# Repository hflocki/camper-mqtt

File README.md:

<p align="center">
  <picture>
    <source media="(prefers-color-scheme: dark)" srcset="docs/logo/vannode-logo-dark.svg">
    
  </picture>
</p>

# VanNode

🇬🇧 English · 🇩🇪 [Deutsch](README.de.md)

Electronics for a camper van that work together over **MQTT**: tanks, temperatures, batteries, heater, roof fan, roof hatch, levelling and two displays. Every device is an ESP8266/ESP32 with its own **Arduino** firmware, its own web interface and Home Assistant discovery. Devices and displays talk to each other directly through the broker, e.g. the MQTT broker of the LTE router. Home Assistant can listen in, but it does not have to run.

## Why?

It all started with Home Assistant and ESPHome. For the camper, that became too much over time: a server that has to run before anything shows up, a YAML configuration per device, updates that change things on the side, and many parts that all have to fit together. A vehicle is often off-grid for days and runs on battery, so I wanted something simpler and more robust.

So the rules here are:

- **Every device works on its own** – with its own web interface for settings and values, even without a display and without a server.
- **MQTT is the only link.** The broker runs on the router anyway. The displays read straight from the broker.
- **Home Assistant is an option, not a requirement.** Discovery is built in; if you use HA, all devices show up automatically.
- **Updates in the browser**, with a check of the file and a fallback to the previous firmware if something goes wrong.

This is not criticism of ESPHome or Home Assistant – both are great. For this one vehicle a leaner setup simply fit better.

```mermaid
flowchart LR
  broker(("MQTT broker<br/>e.g. RUT956"))
  tank["tanklevel<br/>fresh, grey, gas"] --> broker
  temp["temp<br/>DS18B20 + alarms"] --> broker
  bat["battery<br/>BMS over Bluetooth"] --> broker
  tool["toolbox<br/>Bluetooth plugins: roof hatch …"] <--> broker
  heater["heater<br/>Truma Combi (LIN)"] <--> broker
  fan["maxxfan<br/>VanTurtle"] <--> broker
  level["level<br/>BNO085 + wedges"] <--> broker
  omg["omg<br/>BLE thermometers"] -.-> broker
  broker <--> display["display<br/>4-inch wall panel + web page"]
  broker --> rb["roadbuddy<br/>M5Stack Core2"]
  broker -.- ha["Home Assistant<br/>(optional)"]
```

## Devices

| Folder | Hardware | Purpose | Base topic |
| --- | --- | --- | --- |
| [`firmware/tanklevel`](firmware/tanklevel) | ESP32-C3 | Fresh and grey water (Votronic), gas bottle (BLE) | `camper/tanklevel` |
| [`firmware/temp`](firmware/temp) | ESP8266 / ESP32-C3 | up to 8 DS18B20 (fridge, freezer …) with alarm limits | `camper/temp` |
| [`firmware/battery`](firmware/battery) | ESP32-C3 | Battery BMS over Bluetooth (Daly, Ective BM X): state of charge, current, cells | `camper/battery` |
| [`firmware/toolbox`](firmware/toolbox) | ESP32-C3 | Bluetooth devices as plugins: RV Tech roof hatch (Heki), CaraWater pump, WCS fridge | `camper/toolbox` |
| [`firmware/heater`](firmware/heater) | ESP32 + LIN transceiver | Truma Combi / Vario Heat as an iNet Box on the CP Plus | `camper/heater` |
| [`firmware/maxxfan`](firmware/maxxfan) | ESP32-C3 + VanTurtle | MaxxFan roof fan | `camper/maxxfan` |
| [`firmware/level`](firmware/level) | ESP32 + BNO085 | Pitch, roll and wedge height for every wheel (fork of the level sensor by klehnst) | `camper/level` |
| [`firmware/omg`](firmware/omg) | ESP32 / ESP32-C3 | Bluetooth thermometers (Govee, Ruuvi, Xiaomi …) through OpenMQTTGateway | `camper/OMG` |
| [`firmware/display`](firmware/display) | Guition ESP32-4848S040 | 4" wall panel + the same page for the phone: shows and controls everything, weather, warnings, Pushover | `camper/display` |
| [`firmware/roadbuddy`](firmware/roadbuddy) | M5Stack Core2 | small battery display: levelling, water, gas | – (receive only) |

Not in this repo: **router data (GPS, mobile signal)** is sent by the RUT956 itself over MQTT, see [router data in the display README](firmware/display/README.md#router-daten-rut956).

- **Testing at home:** [`tools/emulator`](tools/emulator) is a Python tool with a local web page. It sends the topics of all devices, the router and Zigbee with values you can change, plus scenarios (tanks running empty, departure, a device dropping out …), so the displays can be tested without the vehicle
- All topics at a glance: [`docs/TOPICS.md`](docs/TOPICS.md)
- Clickable mockups of every web interface: [`docs/mockups/`](docs/mockups/index.html)
- Notes for AI assistants and contributors: [`AGENTS.md`](AGENTS.md)

The documentation of the individual devices and the web interfaces are in German.

## Quick start

1. **Get the firmware:** download the device's `.bin` from [Releases](https://github.com/hflocki/vannode/releases) – or build it yourself (Arduino IDE or `arduino-cli`; board and libraries are listed in the device README).
2. **Flash once over USB.** After that, updates go through the web interface.
3. **Set up:** without WiFi credentials the device opens an access point `<device>-Node-XXXXXX`. Connect, open `http://192.168.4.1`, enter WiFi and MQTT broker.
4. The device appears under `camper/<device>/…` on the broker; the display finds it by itself.

## Common rules

All devices follow the same scheme, so the displays and Home Assistant understand them without special cases:

| What | How |
| --- | --- |
| Topics | `camper/<device>/…`, values **retained** |
| Availability | `camper/<device>/status` = `online` / `offline` as last will (retained, QoS 1) |
| Diagnostics | `camper/<device>/info`: JSON with version, IP, signal, uptime |
| Commands | `…/cmd/…` or `…/set/…`, not retained |
| Home Assistant | auto discovery under `homeassistant/…`, one device per firmware |
| Setup | access point `<device>-Node-XXXXXX`, settings in the browser at `http://192.168.4.1` |
| Web interface | same look on every device, optional login (HTTP basic auth); forgot the login → `noauth` in the serial monitor or factory reset |
| Updates | in the browser, with checks (wrong device, `.merged.bin`, too large), event log and fallback to the previous firmware |
| Firmware version | `FW_VERSION` in the device's `config.h`, shown in the web UI and in HA |

## Your own settings (`config_local.h`)

Passwords, WiFi and broker do not belong in the repo. Next to its `config.h`, every device has a template `config_local.h.example`:

```bash
cd firmware/temp/camper_temp
cp config_local.h.example config_local.h   # then edit
```

Everything in `config_local.h` replaces the default from `config.h`. The file is excluded by `.gitignore`, so it never ends up on GitHub, and updates or patches do not overwrite it. Typical values:

| Value | Effect |
| --- | --- |
| `DEFAULT_AP_PASSWORD` | password of the setup access point |
| `DEFAULT_OTA_PASSWORD` | password for updates through the network port of the Arduino IDE |
| `DEFAULT_WIFI_SSID` / `DEFAULT_WIFI_PASSWORD` | WiFi a freshly flashed device joins right away |
| `DEFAULT_MQTT_SERVER`, `_USER`, `_PASSWORD` | factory broker |
| `DEFAULT_WEB_USER` / `DEFAULT_WEB_PASSWORD` | factory login for the web interface |

Any other value from `config.h` can be overridden as well (pins, prefix, tank size …).

Note: factory WiFi, MQTT and login only apply while nothing is stored on the device yet. A normal update over existing settings does not change them. They are taken over again after a **factory reset** in the web UI, after flashing with **Erase All Flash Before Sketch Upload: Enabled** (Arduino IDE, Tools menu), or for temp, tanklevel, level and battery after uploading the LittleFS image. The access point and OTA passwords always apply immediately.

The Road Buddy has no settings page, only an update page; there the whole `config.h` is the personal file (template `config.example.h`). A firmware built with your own `config.h` stores the credentials in flash, so the Actions firmware can be installed through the update page afterwards.

## Warnings

`firmware/temp` reports exceeded limits (e.g. "fridge above 8 °C for 15 min") under `camper/temp/alarm_text`. The wall panel shows these, heater errors and battery, tank, frost and weather warnings in the status tile and as a yellow banner in the header – optionally also as a **Pushover** message on the phone, with its own priority per kind of warning, up to an emergency that keeps ringing until it is confirmed. Home Assistant gets the same alarms as binary sensors.

## Ready-made firmware

Every push builds all devices with GitHub Actions ([`.github/workflows/build.yml`](.github/workflows/build.yml)), using exactly the board package and library versions from the device READMEs. The `.bin` files are available in the **Actions** tab of each run.

A release for **one** device is made with a tag `<device>-v<version>`:

```bash
git tag temp-v1.1.0
git push origin temp-v1.1.0
```

Then only this device is built and the `.bin` is attached to the release. All devices install it through their web interface (Road Buddy through its update page). For temp, tanklevel, level, battery, maxxfan and toolbox the web interface also lives as `data/index.html.gz` in the sketch folder and is uploaded separately after an update.

**Names:** every device is called `<device>-node` – hostname (`temp-node.local`), setup access point (`Temp-Node-XXXXXX`) and release file (`temp-node-esp32c3.bin`). MQTT topics stay `camper/<device>/…`, Home Assistant IDs stay unchanged.

**All devices in one release:** a tag `bundle-v<version>` builds every device and creates one release with the files listed in [`.github/bundle.txt`](.github/bundle.txt) (one device and target per line, e.g. `heater esp32`), plus the web pages as `<device>-node-web.html.gz` and a table of all versions.

```bash
git tag bundle-v2026.11.07
git push origin bundle-v2026.11.07
```

## Build just one device

Take the device folder and follow its README. If you do not want the whole repo:

```bash
git clone --filter=blob:none --sparse https://github.com/hflocki/vannode.git
cd vannode
git sparse-checkout set firmware/temp
```

## New device

[`firmware/_template`](firmware/_template) is a working sample device with everything shared (WiFi with setup access point, web interface, settings, MQTT with Home Assistant discovery, updates without USB). One command copies it as a new device; then you only fill in the sensor part (`sensor.cpp`). Guide (German): [`firmware/_template/ANLEITUNG.md`](firmware/_template/ANLEITUNG.md).

```bash
python firmware/_template/tools/new_device.py waste "Abwasser"
```

Every folder is complete on its own: its own README with hardware, board settings, libraries and topics, the Arduino sketch in a subfolder named like the `.ino` (e.g. `camper_temp/`, heater `truma_heater/`). Everything is built with Arduino (IDE or `arduino-cli`); PlatformIO is only used for the Bluetooth gateway `firmware/omg`, because OpenMQTTGateway is a third-party PlatformIO project.

## Mockups

[`docs/mockups/`](docs/mockups/index.html) has a clickable mockup of every web interface: the real page from the firmware with simulated data. Buttons, settings, saving and uploads react like on the device, but nothing is sent. `index.html` shows all devices side by side in phone size. The design draft that all pages follow (colours, type, icons, building blocks, plus drafts of the display page) is in [`docs/mockups/design/`](docs/mockups/design/system.html) and linked from the same index.

To view them, download the folder and open `index.html` in a browser. Regenerate after changing a web interface (Python standard library only, no venv needed):

```bash
python3 tools/mockups/make_mockups.py
```

Sample data and simulated behaviour per device are in `tools/mockups/mock/<device>.js`, the shared part (fetch, WebSocket, upload) in `core.js`. For a new device, add a file there and register it in `make_mockups.py`. The Road Buddy only has a small update page and is therefore missing.

## Origin

The devices used to be separate repos (`camper-tanklevel`, `camper-temp`, `camper-heater`, `camper-maxxfan`, `camper-display`, `m5core2-roadbuddy`, `camper_toolbox`). They were moved here; the old repos are or will be archived.

## Licenses

Every folder keeps its license:

| Folder | License |
| --- | --- |
| `firmware/battery` | Apache-2.0 (protocols ported from [aiobmsble](https://github.com/patman15/aiobmsble)) |
| `firmware/heater` | GPL-3.0 (protocol logic ported from GPL projects, see its README) |
| `firmware/level` | MIT ([klehnst](https://github.com/klehnst/ESP32-Adrafruit-BNO085-HomeAssistant-Caravan-Levelsensor-MQTT)) |
| `firmware/tanklevel`, `temp`, `maxxfan`, `display` | MIT |
| `firmware/toolbox` | MIT (roof hatch protocol ported from the HA integration rvtech-hacs) |
| `firmware/roadbuddy` | MIT |

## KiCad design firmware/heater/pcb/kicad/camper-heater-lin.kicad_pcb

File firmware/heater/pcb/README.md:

# camper-heater LIN – eigene Platine

Fertig bestückbare Platine für die camper-heater-Firmware: ESP32-C3-Modul, LIN-Transceiver, geschützte 12-V-Versorgung, USB-C zum Flashen und zwei RJ12-Buchsen. Der ESP meldet sich wie eine iNet Box als **Slave** an, das **CP Plus bleibt Master** und voll bedienbar.

> **Stand: Version 1.0, noch nicht gefertigt und nicht getestet.** Die Daten bestehen den Design-Check von KiCad (keine Fehler, alle Verbindungen geroutet). Für die erste Bestellung die kleinste Stückzahl wählen (5 Platinen, 2 davon bestückt) und vor dem Einbau die Prüfschritte unten machen.

| Oberseite | Unterseite |
| --- | --- |
|  |  |

Schaltplan: [`docs/schaltplan.pdf`](docs/schaltplan.pdf) · Gerber-Vorschau: [`docs/ansicht-gerber.png`](docs/ansicht-gerber.png)

## Was drauf ist

| Block | Bauteile | Zweck |
| --- | --- | --- |
| 12-V-Eingang | J1 Schraubklemme, **F1 Mini-Flachsicherung 1 A**, D1 Verpolschutz (Schottky 100 V), D2 TVS SMBJ22A | Kurzschluss, Verpolung und Spannungsspitzen beim Motorstart oder Laden |
| Versorgung | PS1 RECOM R-78HB5.0-0.5 (9–72 V → 5 V), D3/D4 + U3 AP2112K-3.3 | fertiges Wandler-Modul für Fahrzeugbordnetze, 3,3 V für den ESP. Strom wahlweise aus 12 V **oder** USB |
| ESP32 | U1 ESP32-C3-WROOM-02-N4, Taster RESET und BOOT, 3 LEDs | Antenne am Platinenrand, darunter kein Kupfer |
| LIN | U2 TJA1021T/20, C11 220 pF, Pull-ups | Slave-Beschaltung ohne Master-Widerstand, wie eine iNet Box |
| Bus | J2 + J3 RJ12 6P6C, alle 6 Kontakte 1:1 verbunden | Pin 3 = LIN, Pin 5 = Masse (wie bei havanti/esphome-truma) |
| USB-C | J4, U4 USBLC6-2SC6 | Flashen, serielles Log, Strom am Schreibtisch |

Maße: **75 × 66 mm**, 2 Lagen, 4 Befestigungslöcher M3. GPIO-Belegung: GPIO4 = LIN TX, GPIO3 = LIN RX, GPIO5 = SLP, GPIO6 = LED LIN (blau), GPIO7 = LED MQTT (gelb), grüne LED = 3,3 V vorhanden.

## Bestellen bei PCBWay

Dateien in [`fertigung/`](fertigung):

| Datei | Wohin bei PCBWay |
| --- | --- |
| `camper-heater-lin-gerber.zip` | „Quick-order PCB“ → **Add Gerber File** |
| `camper-heater-lin-bom.xlsx` | Assembly → **BOM** |
| `camper-heater-lin-cpl.csv` | Assembly → **Centroid / Pick & Place** |

**Platine** (Werte, die PCBWay beim Gerber meist selbst erkennt):
- Layers: **2**, Size: **75 × 66 mm**, Material: FR-4 TG130–150, Thickness: **1,6 mm**
- Min track/spacing: **6/6 mil** (Design nutzt 0,2 mm), Min hole size: **0,3 mm**
- Solder mask: beliebig (z. B. grün), Silkscreen: weiß, Surface finish: **HASL lead free**
- Copper weight: 1 oz, Via: tented, keine Sonderoptionen

**Bestückung** (Assembly Service anhaken):
- **Turnkey** (PCBWay besorgt alle Teile), Assembly side: **Top side**
- Number of unique parts: **28**, SMD-Teile **und** Through-Hole-Teile (J1, J2, J3, F1, PS1) → „Both“
- Quantity: z. B. **2**
- Bemerkung, die man ins Feld „Notes“ kopieren kann:
  > Please do not place JP1 (open solder jumper) and test points TP1–TP5, they are pads only. Fuse holder F1: only the holder (Keystone 3568), no fuse. Fiducials FID1/FID2 on top side. Please check the rotation of U1, U2, U3, U4 and the diodes against the silkscreen marks.

PCBWay prüft BOM und Bestückungsdatei vor der Fertigung und meldet sich bei Rückfragen, z. B. wenn ein Teil nicht lieferbar ist und ein Ersatz vorgeschlagen wird. Gleichwertige Ersatzteile sind in Ordnung, solange **Spannungsfestigkeit und Gehäuse** gleich bleiben (D2 SMBJ22A, C1 50 V, PS1 R-78HB5.0-0.5).

**Dazu kaufen:** eine Mini-Flachsicherung (ATM) **1 A**, ein kurzes RJ12-Kabel 6P6C (6 Adern, nicht nur 4), Kabel für 12 V und Masse.

## Vor dem ersten Einbau prüfen

1. **Sichtprüfung:** D1, D2 (Strich = Kathode) und U1–U4 wie auf dem Bestückungsdruck.
2. **Ohne Sicherung** mit dem Multimeter messen: J1 Pin 1 gegen Pin 2 darf **kein Kurzschluss** sein, ebenso TP1 (VBAT), TP2 (5 V) und TP3 (3,3 V) gegen TP4 (GND).
3. **Nur USB** anstecken (ohne 12 V): grüne LED an, TP3 ≈ 3,3 V. Firmware flashen (siehe unten).
4. **12 V über ein Labornetzteil mit Strombegrenzung** (z. B. 100 mA) oder direkt mit eingesetzter 1-A-Sicherung: TP1 ≈ 11,7 V, TP2 ≈ 4,7 V, TP3 = 3,3 V. Strom im Leerlauf rund 30–80 mA bei 12 V.
5. **RJ12-Kabel messen, bevor JP1 geschlossen wird:** Im Fahrzeug bei eingeschaltetem CP Plus am freien RJ12-Anschluss messen. Pin 5 muss 0 V gegen Fahrzeugmasse haben, Pin 3 (LIN) liegt in Ruhe bei etwa Bordspannung. **JP1 bleibt offen**, die Masse kommt über J1. Nur wenn die Verbindung ohne JP1 nicht klappt und Pin 5 nachgemessen Masse ist, JP1 mit einem Lötklecks schließen.

## Anschluss im Camper

- **Einfachster Weg:** Nur **J2** benutzen und mit einem RJ12-Kabel an die **freie Zubehörbuchse der Combi** stecken (dort steckt sonst die iNet Box). J3 bleibt frei.
- **Durchschleifen:** CP Plus → J2 und J3 → Heizung. Die Platine verhält sich dann wie ein 6-poliger Y-Verteiler. Dafür beide Kabel gleicher Art nehmen (beide 1:1 oder beide gekreuzt).
- **12 V:** J1 Pin 1 (+12 V) mit Plus aus dem Sicherungsverteiler, Pin 2 mit Masse. Die 1-A-Sicherung sitzt auf der Platine; eine zweite Sicherung am Verteiler schadet nicht.

## Firmware

Im Sketch [`../truma_heater/config.h`](../truma_heater/config.h) das Board-Profil wählen, am besten in `config_local.h`:

```cpp
#define BOARD_CAMPER_LIN_C3
```

Arduino IDE: Board **ESP32C3 Dev Module**, USB CDC On Boot **Enabled**, Partition Scheme **Minimal SPIFFS**. Zum ersten Flashen BOOT gedrückt halten, RESET kurz drücken, BOOT loslassen. Danach geht jedes Update per Web-UI oder OTA.

Am CP Plus einmal anmelden: Einstellungen → **RESET → PR SET**. Siehe [Inbetriebnahme](../README.md#inbetriebnahme).

## Selbst ändern

Die Platine wird komplett aus Skripten erzeugt, damit Änderungen nachvollziehbar bleiben:

| Datei | Inhalt |
| --- | --- |
| `tools/parts.py` | Bauteile, Teilenummern und alle Verbindungen (eine Quelle für Platine, BOM und Schaltplan) |
| `tools/place.py` | Positionen, Platinenumriss, Netzklassen, Beschriftung |
| `tools/route.py` | Autorouter (Freerouting) und Import |
| `tools/finish.py` | Masseflächen oben und unten, Durchkontaktierungen |
| `tools/make_outputs.py` | Gerber, Bohrdaten, BOM, Bestückungsdatei |
| `tools/schematic.py` | Schaltplan als PDF/SVG |
| `kicad/camper-heater-lin.kicad_pcb` | fertige Platine zum Öffnen in KiCad 7 oder neuer |

Neu bauen (Linux mit KiCad 7, Java 17+ und `xvfb-run`):

```bash
cd firmware/heater/pcb/tools
curl -LO https://github.com/freerouting/freerouting/releases/download/v1.9.0/freerouting-1.9.0.jar && mv freerouting-1.9.0.jar freerouting.jar
python3 -m venv --system-site-packages .venv && source .venv/bin/activate && pip install -r requirements.txt
./build_all.sh
```

Kleine Änderungen (Beschriftung, eine Leiterbahn) gehen auch direkt in KiCad an `kicad/camper-heater-lin.kicad_pcb`; danach in KiCad den Design-Check laufen lassen und die Fertigungsdateien neu exportieren.

## Lizenz

Wie der Rest von `firmware/heater`: GPL-3.0.

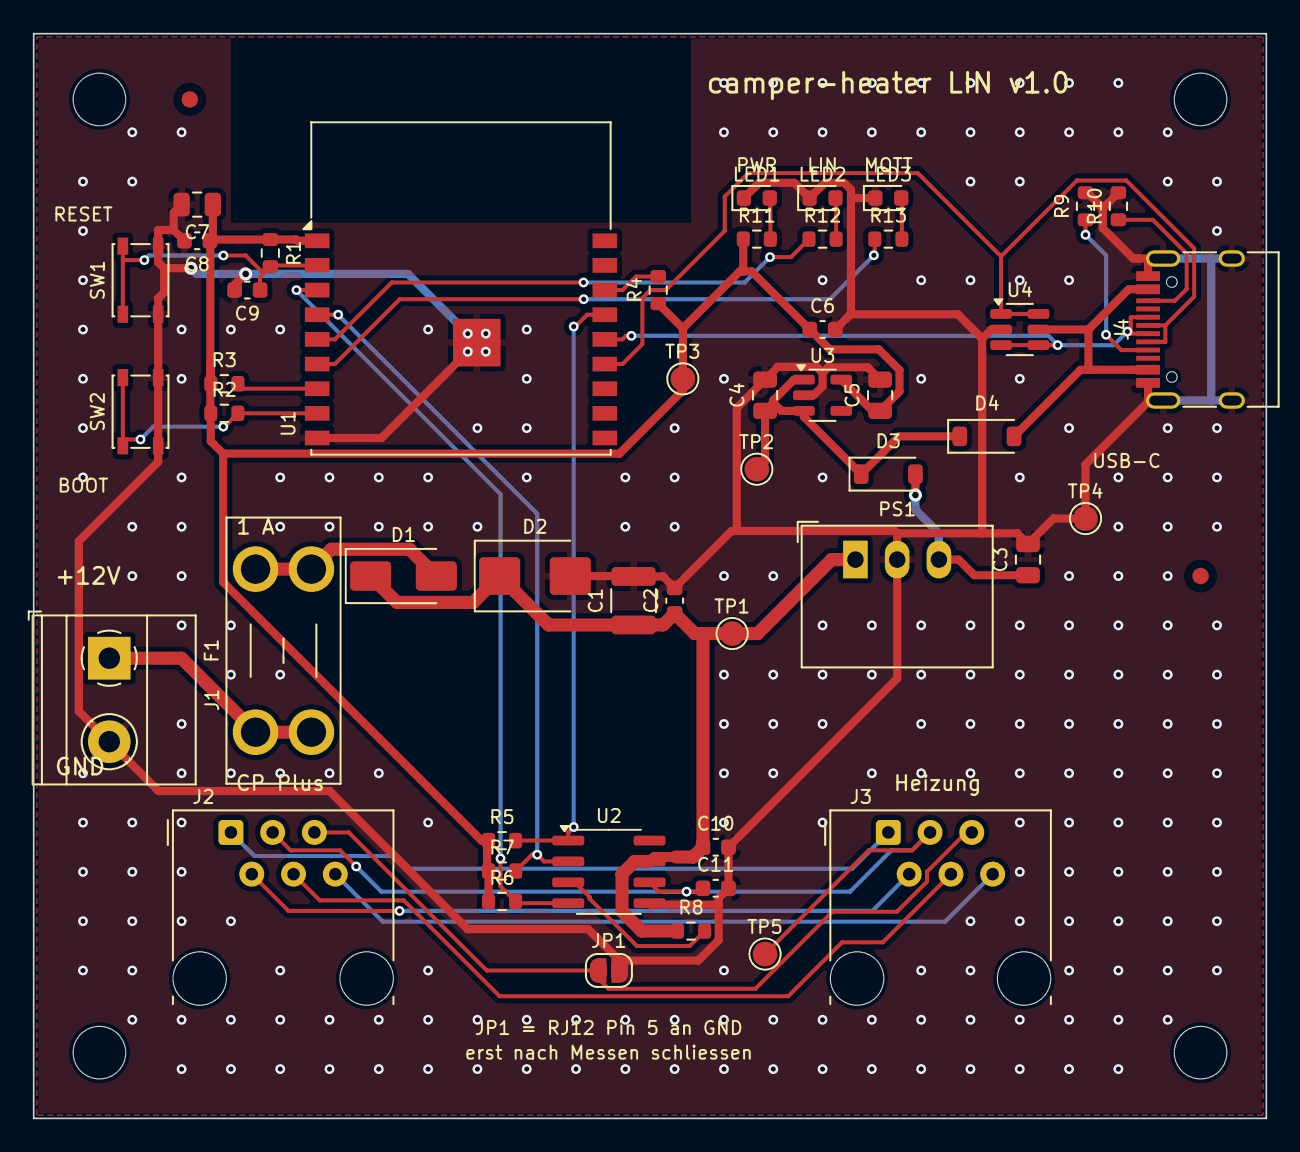
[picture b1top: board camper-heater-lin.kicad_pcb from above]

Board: 2 copper layers, 75.0 x 66.0 mm, 55 parts (0 on the bottom side), 31 nets.

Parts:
C1: 10uF 50V; C_1210_3225Metric
C2, C6, C8, C10: 100nF 50V; C_0603_1608Metric
C3, C5, C7: 22uF 10V; C_0805_2012Metric
C4: 10uF 10V; C_0805_2012Metric
C9: 1uF; C_0603_1608Metric
C11: 220pF 50V; C_0603_1608Metric
D1: B1100; D_SMA
D2: SMBJ22A; D_SMB
D3, D4: B5819W; D_SOD-123
F1: Mini-Flachsicherung 1 A; Fuseholder_Blade_Mini_Keystone_3568
FID1, FID2: Fiducial; Fiducial_1mm_Mask2mm
H1, H2, H3, H4: M3; MountingHole_3.2mm_M3
J1: 12V IN; TerminalBlock_Phoenix_MKDS-1,5-2-5.08_1x02_P5.08mm_Horizont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
J2: RJ12 (CP Plus); RJ12_Amphenol_54601-x06_Horizontal
J3: RJ12 (Heizung); RJ12_Amphenol_54601-x06_Horizontal
J4: USB-C; USB_C_Receptacle_HRO_TYPE-C-31-M-12
JP1: RJ12 Pin 5 an GND; SolderJumper-2_P1.3mm_Open_RoundedPad1.0x1.5mm
LED1: grün (Power); LED_0603_1608Metric
LED2: blau (LIN); LED_0603_1608Metric
LED3: gelb (MQTT); LED_0603_1608Metric
PS1: R-78HB5.0-0.5; Converter_DCDC_RECOM_R-78HB-0.5_THT
R1, R2, R3, R4, R6, R7, R8: 10k; R_0603_1608Metric
R5: 4.7k; R_0603_1608Metric
R9, R10: 5.1k; R_0603_1608Metric
R11, R12, R13: 1k; R_0603_1608Metric
SW1: RESET; SW_SPST_PTS810
SW2: BOOT; SW_SPST_PTS810
TP1: VBAT; TestPoint_Pad_D1.5mm
TP2: 5V; TestPoint_Pad_D1.5mm
TP3: 3V3; TestPoint_Pad_D1.5mm
TP4: GND; TestPoint_Pad_D1.5mm
TP5: LIN; TestPoint_Pad_D1.5mm
U1: ESP32-C3-WROOM-02-N4; ESP32-C3-WROOM-02
U2: TJA1021T/20; SOIC-8_3.9x4.9mm_P1.27mm
U3: AP2112K-3.3; SOT-23-5
U4: USBLC6-2SC6; SOT-23-6

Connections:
+3V3: C5.1, C6.1, C7.1, C8.1, R1.1, R2.1, R3.1, R4.1, R5.1, R6.1, R7.1, R11.1, TP3.1, U1.1, U3.5
+5V: C4.1, D3.1, D4.1, TP2.1, U3.1, U3.3
+5V_DC: C3.1, D3.2, PS1.3
CC1: J4.A5, R9.1
CC2: J4.B5, R10.1
EN: C9.1, R1.2, SW1.1, U1.2
GND: C1.2, C2.2, C3.2, C4.2, C5.2, C6.2, C7.2, C8.2, C9.2, C10.2, C11.2, D2.2, J1.2, J4.A1, J4.A12, J4.B1, J4.B12, J4.S1, JP1.2, LED1.1, LED2.1, LED3.1, PS1.2, R9.2, R10.2, SW1.2, SW2.2, TP4.1, U1.9, U1.19, U2.5, U3.2, U4.2
IO2: R4.2, U1.16
IO8: R3.2, U1.7
IO9: R2.2, SW2.1, U1.8
LED1_A: LED1.2, R11.2
LED2_A: LED2.2, R12.2
LED3_A: LED3.2, R13.2
LED_LIN: R12.1, U1.5
LED_MQTT: R13.1, U1.6
LIN: C11.1, J2.3, J3.3, TP5.1, U2.6
LIN_RX: R5.2, U1.15, U2.1
LIN_SLP: R7.2, U1.4, U2.2
LIN_TX: R6.2, U1.3, U2.4
LIN_WAKE: R8.2, U2.3
RJ1: J2.1, J3.1
RJ2: J2.2, J3.2
RJ4: J2.4, J3.4
RJ5: J2.5, J3.5, JP1.1
RJ6: J2.6, J3.6
USB_DN: J4.A7, J4.B7, U1.13, U4.1, U4.6
USB_DP: J4.A6, J4.B6, U1.14, U4.3, U4.4
VBAT: C1.1, C2.1, C10.1, D1.1, D2.1, PS1.1, R8.1, TP1.1, U2.7
VBUS: D4.2, J4.A4, J4.A9, J4.B4, J4.B9, U4.5
VIN_F: D1.2, F1.2
VIN_RAW: F1.1, J1.1

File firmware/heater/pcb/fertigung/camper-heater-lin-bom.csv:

Item #,Designator,Qty,Manufacturer,Mfg Part #,Description / Value,Package / Footprint,Type,Hinweis
1,C1,1,Murata,GRM32ER71H106KA12L,10uF 50V – Keramikkondensator,C_1210_3225Metric,SMD,
2,"C2,C6,C8,C10",4,Murata,GRM188R71H104KA93D,100nF 50V – Keramikkondensator,C_0603_1608Metric,SMD,
3,"C3,C5,C7",3,Murata,GRM21BR61A226ME44L,22uF 10V – Keramikkondensator,C_0805_2012Metric,SMD,
4,C4,1,Murata,GRM21BR61A106KE19L,10uF 10V – Keramikkondensator,C_0805_2012Metric,SMD,
5,C9,1,Murata,GRM188R71C105KA12D,1uF – Keramikkondensator,C_0603_1608Metric,SMD,
6,C11,1,Murata,GRM1885C1H221JA01D,220pF 50V – Keramikkondensator,C_0603_1608Metric,SMD,
7,D1,1,Diodes Inc.,B1100-13-F,"B1100 – Schottky 100 V 1 A, Verpolschutz",D_SMA,SMD,
8,D2,1,Littelfuse,SMBJ22A,"SMBJ22A – TVS 22 V, Schutz gegen Spannungsspitzen",D_SMB,SMD,
9,"D3,D4",2,Diodes Inc.,B5819W,B5819W – Schottky 40 V 1 A (Wandler -> 5 V),D_SOD-123,SMD,
10,F1,1,Keystone,3568,"Mini-Flachsicherung 1 A – Sicherungshalter Mini-Flachsicherung (ATM), Sicherung 1 A lose dazu",Fuseholder_Blade_Mini_Keystone_3568,THT,"Nur der Halter wird bestückt. Sicherung 1 A (Mini-Flachsicherung ATM, z. B. Littelfuse 0297001.WXNV) lose beilegen oder selbst einstecken."
11,J1,1,Phoenix Contact,1715734,"12V IN – Schraubklemme 2-pol. 5,08 mm (1 = +12 V, 2 = Masse)","TerminalBlock_Phoenix_MKDS-1,5-2-5.08_1x02_P5.08mm_Horizontal",THT,
12,J2,1,Amphenol,54601-906WPLF,RJ12 (CP Plus) – RJ12 6P6C Buchse,RJ12_Amphenol_54601-x06_Horizontal,THT,
13,J3,1,Amphenol,54601-906WPLF,RJ12 (Heizung) – RJ12 6P6C Buchse,RJ12_Amphenol_54601-x06_Horizontal,THT,
14,J4,1,Korean Hroparts,TYPE-C-31-M-12,USB-C – USB-C Buchse 16-pol.,USB_C_Receptacle_HRO_TYPE-C-31-M-12,SMD,
15,LED1,1,Würth,150060VS75000,grün (Power) – LED grün,LED_0603_1608Metric,SMD,
16,LED2,1,Würth,150060BS75000,blau (LIN) – LED blau,LED_0603_1608Metric,SMD,
17,LED3,1,Würth,150060YS75000,gelb (MQTT) – LED gelb,LED_0603_1608Metric,SMD,
18,PS1,1,RECOM,R-78HB5.0-0.5,"R-78HB5.0-0.5 – Schaltregler-Modul 9-72 V -> 5 V 0,5 A",Converter_DCDC_RECOM_R-78HB-0.5_THT,THT,
19,"R1,R2,R3,R4,R6,R7,R8",7,Yageo,RC0603FR-0710KL,"10k – Widerstand 1 %, 0603",R_0603_1608Metric,SMD,
20,R5,1,Yageo,RC0603FR-074K7L,"4.7k – Widerstand 1 %, 0603",R_0603_1608Metric,SMD,
21,"R9,R10",2,Yageo,RC0603FR-075K1L,"5.1k – Widerstand 1 %, 0603",R_0603_1608Metric,SMD,
22,"R11,R12,R13",3,Yageo,RC0603FR-071KL,"1k – Widerstand 1 %, 0603",R_0603_1608Metric,SMD,
23,SW1,1,C&K,PTS810 SJM 250 SMTR LFS,RESET – Taster Neustart,SW_SPST_PTS810,SMD,
24,SW2,1,C&K,PTS810 SJM 250 SMTR LFS,BOOT – Taster Boot (Flash-Modus),SW_SPST_PTS810,SMD,
25,U1,1,Espressif,ESP32-C3-WROOM-02-N4,"ESP32-C3-WROOM-02-N4 – WLAN-Modul ESP32-C3, 4 MB Flash",ESP32-C3-WROOM-02,SMD,"Antenne zeigt zum Platinenrand, unter der Antenne kein Kupfer."
26,U2,1,NXP,"TJA1021T/20/C,118",TJA1021T/20 – LIN-Transceiver,SOIC-8_3.9x4.9mm_P1.27mm,SMD,"Gleichwertig: TJA1021T/20/C,118 oder TJA1021T/10 (LIN 2.x Slave)."
27,U3,1,Diodes Inc.,AP2112K-3.3TRG1,"AP2112K-3.3 – LDO 3,3 V 600 mA",SOT-23-5,SMD,
28,U4,1,STMicroelectronics,USBLC6-2SC6,USBLC6-2SC6 – ESD-Schutz USB,SOT-23-6,SMD,

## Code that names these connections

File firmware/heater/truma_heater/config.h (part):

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    !defined(BOARD_ESP32_DEVKIT)
// #define BOARD_SMARTAVAN       // smartavan heater controller (Arduino board: "ESP32 Dev Module")
// #define BOARD_ESP32_GENERIC   // ESP32 DevKit + TJA1020/1021 module, inetbox2mqtt wiring (Arduino board: "ESP32 Dev Module")
// #define BOARD_ESP32_DEVKIT    // ESP32 DevKit (WROOM-32) + LIN module, TX 16 / RX 17 (Arduino board: "ESP32 Dev Module")
// #define BOARD_ESP32S3_GENERIC // ESP32-S3 DevKit + LIN module (Arduino board: "ESP32S3 Dev Module")
// #define BOARD_ESP32C3_GENERIC // ESP32-C3 + LIN module (Arduino board: "ESP32C3 Dev Module")
// #define BOARD_ESP32C3_SUPERMINI  // ESP32-C3 Super Mini + LIN module (Arduino board: "ESP32C3 Dev Module")
// #define BOARD_CAMPER_LIN_C3   // own LIN board with ESP32-C3-WROOM-02 + TJA1021 (Arduino board: "ESP32C3 Dev Module")
// Nothing selected: the default board of the chip the sketch is built for (also what CI builds)
#if CONFIG_IDF_TARGET_ESP32
#define BOARD_ESP32_DEVKIT
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#ifndef LIN_UART_NUM
#define LIN_UART_NUM UART_NUM_2
#endif
#ifndef LIN_TX_PIN
#define LIN_TX_PIN 16
#endif
#ifndef LIN_RX_PIN
#define LIN_RX_PIN 17
#endif

#elif defined(BOARD_ESP32_GENERIC)
// Plain ESP32 DevKit + TJA1020/TJA1021 module, wiring as in mc0110/inetbox2mqtt ("ESP32" profile)
#define BOARD_NAME "ESP32 + LIN module"
#ifndef LIN_UART_NUM
#define LIN_UART_NUM UART_NUM_2
#endif
#ifndef LIN_TX_PIN
#define LIN_TX_PIN 17
#endif
#ifndef LIN_RX_PIN
#define LIN_RX_PIN 16
#endif
#ifndef MQTT_LED_PIN
#define MQTT_LED_PIN 4
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#elif defined(BOARD_ESP32_DEVKIT)
// ESP32 DevKit V4 (ESP32-WROOM-32) + TJA1020 module (e.g. FST T151), supplied with 5 V from a buck converter.
// ESP TX GPIO16 -> module TX (TXD), module RX (RXD) -> ESP RX GPIO17. Module SLP to 3V3.
#define BOARD_NAME "Heater Node (ESP32 DevKit + LIN module)"
#ifndef LIN_UART_NUM
#define LIN_UART_NUM UART_NUM_2
#endif
#ifndef LIN_TX_PIN
#define LIN_TX_PIN 16
#endif
#ifndef LIN_RX_PIN
#define LIN_RX_PIN 17
#endif

#elif defined(BOARD_ESP32S3_GENERIC)
// ESP32-S3 DevKit + LIN module (any free GPIOs, adjust with build flags)
#define BOARD_NAME "ESP32-S3 + LIN module"
#ifndef LIN_UART_NUM
#define LIN_UART_NUM UART_NUM_1
#endif
#ifndef LIN_TX_PIN
#define LIN_TX_PIN 17
#endif
#ifndef LIN_RX_PIN
#define LIN_RX_PIN 18
#endif

#elif defined(BOARD_ESP32C3_GENERIC)
// ESP32-C3 (single core, UART0/1 only) + LIN module
#define BOARD_NAME "ESP32-C3 + LIN module"
#ifndef LIN_UART_NUM
#define LIN_UART_NUM UART_NUM_1
#endif
#ifndef LIN_TX_PIN
#define LIN_TX_PIN 21
#endif
#ifndef LIN_RX_PIN
#define LIN_RX_PIN 20
#endif

#elif defined(BOARD_ESP32C3_SUPERMINI)
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#ifndef LIN_UART_NUM
#define LIN_UART_NUM UART_NUM_1
#endif
#ifndef LIN_TX_PIN
#define LIN_TX_PIN 4
#endif
#ifndef LIN_RX_PIN
#define LIN_RX_PIN 3
#endif
#ifndef LIN_LED_PIN
#define LIN_LED_PIN 8  // on-board blue LED
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#endif

#elif defined(BOARD_CAMPER_LIN_C3)
// Own LIN board: ESP32-C3-WROOM-02, TJA1021, RECOM 12 V -> 5 V, LDO 3.3 V. Same LIN pins as the Super Mini build.
#define BOARD_NAME "Heater Node LIN board (ESP32-C3-WROOM-02)"
#ifndef LIN_UART_NUM
#define LIN_UART_NUM UART_NUM_1
#endif
#ifndef LIN_TX_PIN
#define LIN_TX_PIN 4
#endif
#ifndef LIN_RX_PIN
#define LIN_RX_PIN 3
#endif
#ifndef LIN_CS_PIN
#define LIN_CS_PIN 5       // TJA1021 SLP_N, 10k pull-up on the board
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#define MQTT_LED_PIN -1   // on = MQTT connected
#endif
#ifndef LIN_LED_PIN
#define LIN_LED_PIN -1    // flicker = LIN traffic, on = CP Plus polls us
#endif
#ifndef LED_ACTIVE_LOW
#define LED_ACTIVE_LOW false
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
